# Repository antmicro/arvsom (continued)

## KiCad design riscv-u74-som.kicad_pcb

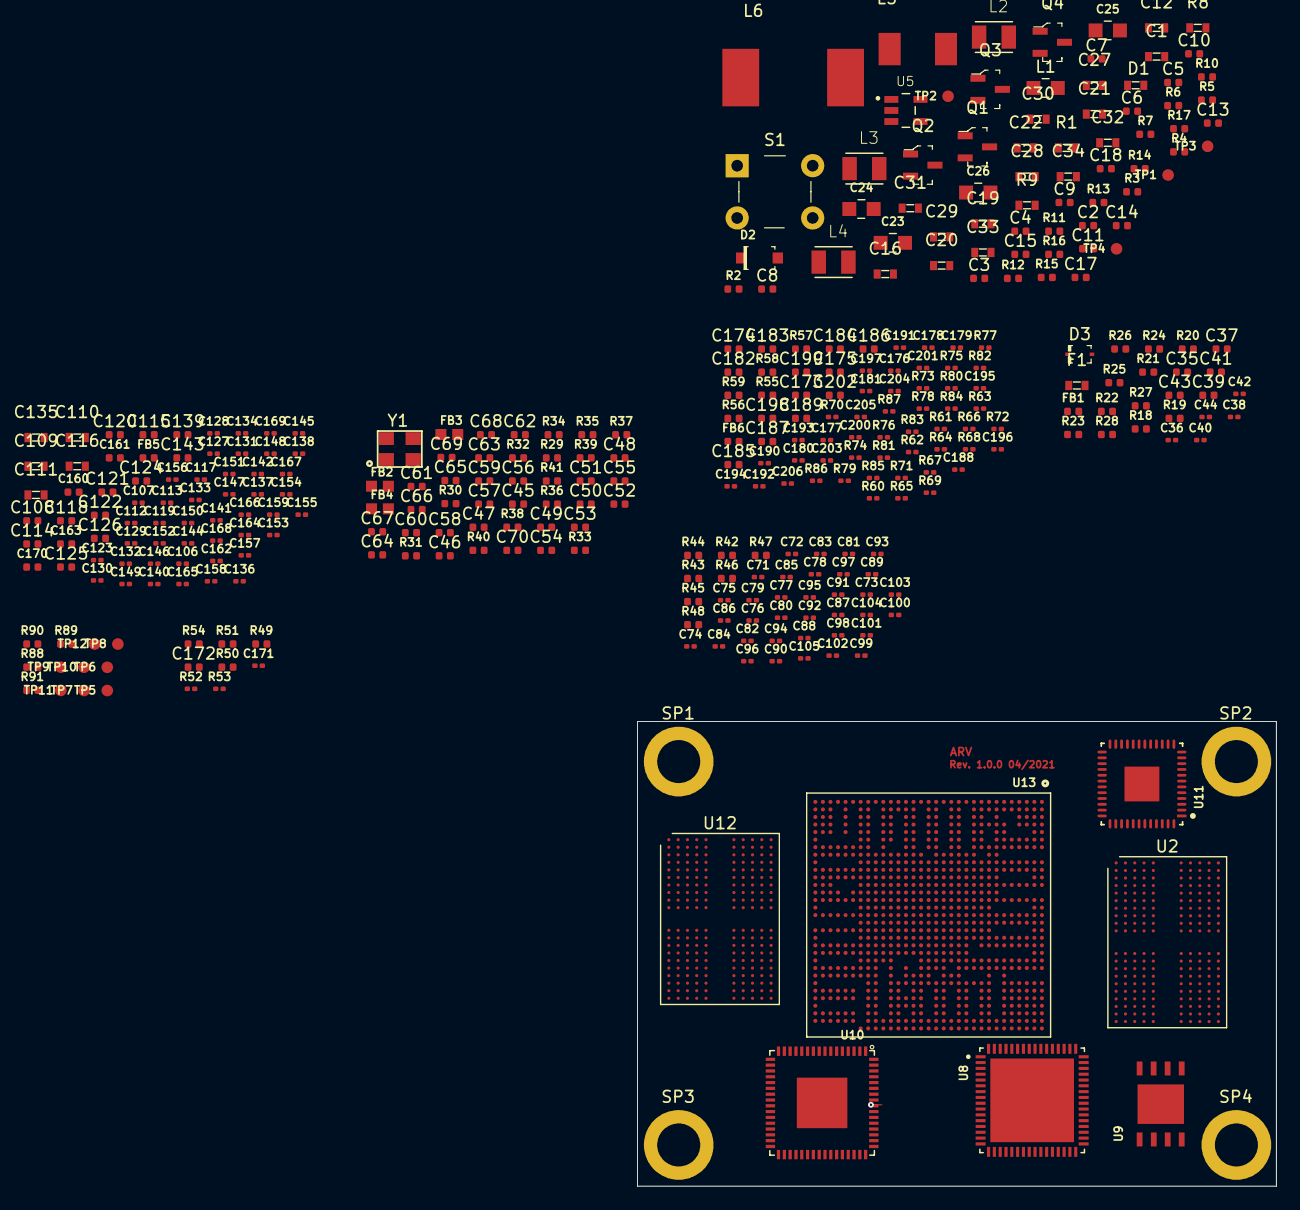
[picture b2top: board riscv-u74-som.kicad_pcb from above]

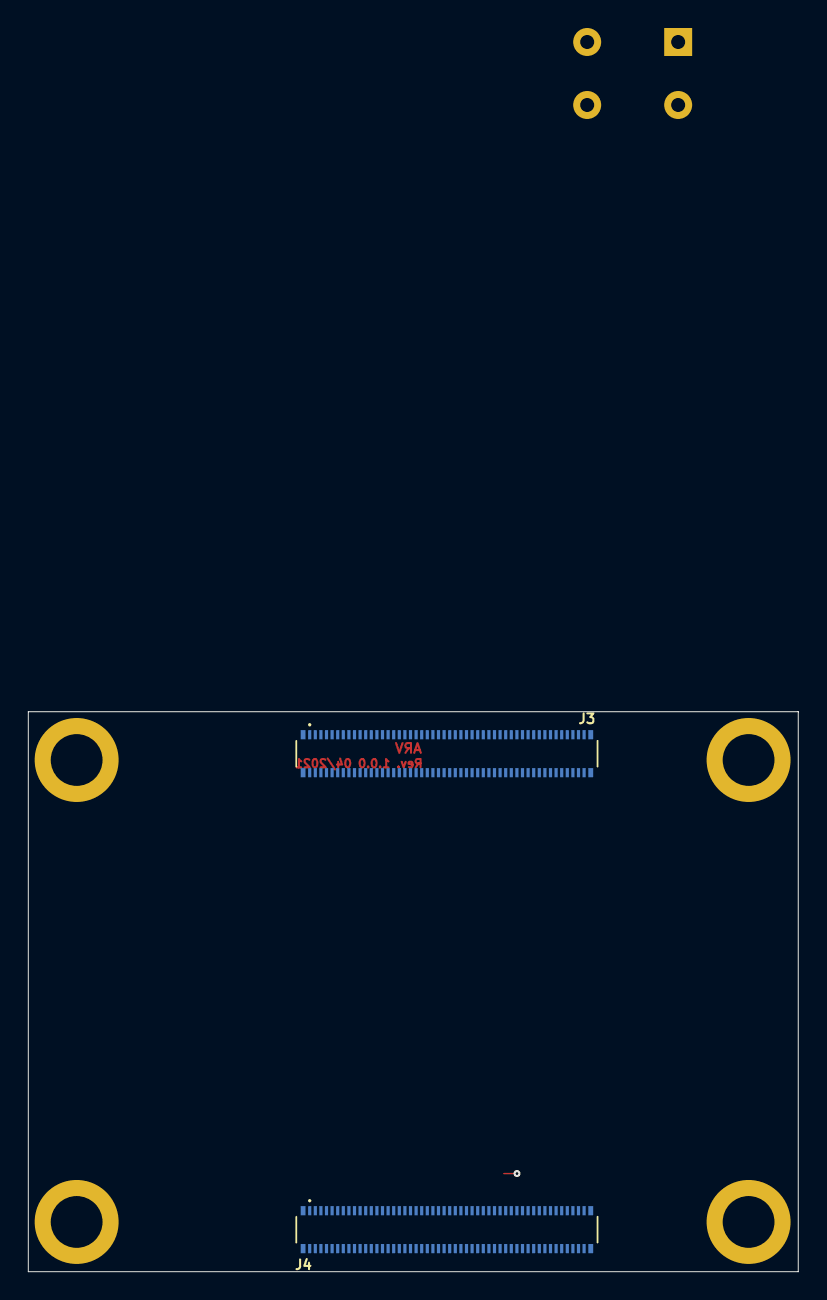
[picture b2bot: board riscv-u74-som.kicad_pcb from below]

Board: 2 copper layers, 55.0 x 40.0 mm, 345 parts (2 on the bottom side), 236 nets.

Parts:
C1, C16, C27, C28: C_10u_0603; 0603-cap
C2, C3, C4, C5, C7, C8, C9, C15, C37, C39, C41, C43: C_2u2_0402; 0402-cap
C6, C11, C14, C45, C47, C49, C50, C58: C_4u7_0402; 0402-cap
C10, C13, C17, C18: C_100n_0402_16V; 0402-cap
C12: C_1n_0603; 0603-cap
C19, C20, C21, C22, C29, C30, C31, C32, C33, C34, C109, C110, C111, C116, C135: C_22u_0603; 0603-cap
C23, C24, C25, C26: C_100u_0805; 0805-cap
C35, C108, C124, C125, C126, C143, C173, C174, C175, C183, C185, C186, C187, C189, C198, C199, C202: C_1u_0402; 0402-cap
C36, C38, C40, C42, C44, C71, C72, C73, C74, C75, C76, C77, C78, C79, C80, C81, C82, C83, C84, C85, C86, C87, C88, C89, C90, C91, C92, C93, C94, C95, C96, C97, C98, C99, C100, C101, C102, C103, C104, C105, C106, C107, C112, C113, C117, C119, C123, C127, C128, C129, C130, C131, C132, C133, C134, C136, C137, C138, C140, C141, C142, C144, C145, C146, C147, C148, C149, C150, C151, C152, C153, C154, C155, C156, C157, C158, C159, C162, C164, C165, C166, C167, C168, C169, C171, C176, C177, C178, C179, C180, C181, C188, C190, C191, C192, C193, C194, C195, C196, C197, C200, C201, C203, C204, C205, C206: C_100n_0201; 0201-res
C46, C48, C51, C52, C53: C_470n_0402; 0402-cap
C54: C_100n_0402; 0402-cap
C55, C56, C57, C59, C60, C61, C62, C63, C64, C65, C66, C67, C68, C172: C_10n_0402; 0402-cap
C69, C70: C_22p_0402; 0402-cap
C114, C115, C118, C120, C121, C122, C139, C182, C184: C_10u_0402; 0402-cap
C160, C161, C163, C170: C_1n_0402; 0402-res
D1: PGB1010603MR
D2: 1N4148W-TP; SOD-123
D3: 1N4148WS; SOD-323F
F1: 0ZCM0002FF2G; 0603-res
FB1, FB5, FB6: BLM15PD121SN1D; 0402-res
FB2, FB3, FB4: BLM18AG601SN1D; 0603
J3, J4: DF40C-100DP-0.4V(51); HRS_DF40C-100DP-0.4V(51)
L1: 10uH; 0805-res
L2, L3, L4: LQH32PN1R0NN0L; IND_LQH32PN1R0NN0L
L5: MPX1D0520LR47
L6: IHLP4040DZERR56M01
Q1, Q2, Q3, Q4: BSS138AKA; SOT-23-3
R1: R_1M_0603; 0603-res
R2, R3, R4, R25, R31, R32, R33, R34, R35, R36, R38, R39, R40, R42, R43, R44, R47, R49, R50, R51, R54, R88, R90: R_10k_0402; 0402-res
R5, R6, R10, R11, R12, R14, R15, R16, R46, R48: R_0R_0402; 0402-res
R7: R_2k2_0402; 0402-res
R8: R_549k_0603; 0603-res
R9: R_13k3_0603; 0603-res
R13, R17, R21, R37: R_4k7_0402; 0402-res
R18, R19, R20, R22, R23, R24, R55, R56, R57, R58, R59: R_33R_0402; 0402-res
R26, R27, R29: R_1k_0402; 0402-res
R28: R_27k_0402; 0402-res
R30: R_12k1_0402; 0402-res
R41: R_1M5_0402; 0402-res
R45, R89, R91: R_240R_0402; 0402-res
R52, R53: R_0R_0201; 0201-res
R60, R61, R62, R63, R64, R65, R66, R67, R68, R69, R70, R71, R72, R73, R74, R75, R76, R77, R78, R79, R80, R81, R82, R83, R84, R85, R86, R87: R_33R_0201; 0201-res
S1: B3F-1000; Switch_Tactile_THT_B3F-1xxx
SP1, SP2, SP3, SP4: 9774030151
TP1, TP2, TP3, TP4, TP5, TP6, TP7, TP8, TP9, TP10, TP11, TP12: TP_SMD1MM; Testpoint_smd_1mm
U2: MT53E256M32D2; BGA-200_10.0x14.5mm_Layout12x22_P0.80x0.65mm
U5: LMR62014XMF_NOPB; SOT95P280X145-5N
U8: TPS65086100; QFN50P900X900X80-65N
U9: GD25LQ256DWIGR; 8-WSON-6x5
U10: TDA19988BHN_C1,557; QFN50P900X900X100-65N
U11: KSZ9031RNXCA; QFN-48-Microchip-QFN77-48LD-PL-2
U12: MT53E256M32D2DS-053; BGA-200_10.0x14.5mm_Layout12x22_P0.80x0.65mm
U13: VIC7100; vic7100
Y1: ABM8G-25.000MHZ-18-D2Y-T; KX-7

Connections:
1V8_OUT: J3.88, J3.90
3V3_OUT: J3.84, J3.86
5V0_IN: J3.77, J3.79, J3.81, J3.83, J3.85, J3.87
/Ethernet/AVDDH: C58.1, C63.1, C66.1, FB2.2, U11.1, U11.12
/Ethernet/AVDDL: C47.1, C51.1, C55.1, C60.1, FB4.1, U11.4, U11.9
/Ethernet/AVDDL_PLL: C50.1, C54.1, C59.1, FB3.1, U11.44
/PMIC/FB: C12.2, R8.2, R9.1, U5.3
ATEMP_TEST0: R51.1, U13.U25
ATEMP_TEST1: R50.1, U13.U24
ATEMP_VCAL: C171.1, U13.V24
ATEMP_VSS: R49.1, U13.V25
AVDD3V3_USB: C202.1, C205.1, FB6.1, U13.AA23
AVDD09_PLL: C108.1, C113.1, C119.1, C123.1, FB5.1, U13.U21, U13.U22, U13.V21
CS0_B: R42.1, U12.R4
CSI1RX_CLK_N: J4.40, U13.M30
CSI1RX_CLK_P: J4.42, U13.M31
CSI1RX_D0_N: J4.28, U13.P30
CSI1RX_D0_P: J4.30, U13.P31
CSI1RX_D1_N: J4.34, U13.N30
CSI1RX_D1_P: J4.36, U13.N31
CSI2RX_CLK_N: J4.27, U13.R30
CSI2RX_CLK_P: J4.29, U13.R31
CSI2RX_D0_N: J4.15, U13.U30
CSI2RX_D0_P: J4.17, U13.U31
CSI2RX_D1_N: J4.21, U13.T30
CSI2RX_D1_P: J4.23, U13.T31
CTL5: D1.2, R4.2, S1.3, S1.4, U8.63
DDR0_A00: U12.H2, U12.R2, U13.C10
DDR0_A01: U12.J2, U12.P2, U13.B10
DDR0_A02: U12.H9, U12.R9, U13.A15
DDR0_A03: U12.H10, U12.R10, U13.D10
DDR0_A04: U12.H11, U12.R11, U13.D12
DDR0_A05: U12.J11, U12.P11, U13.E10
DDR0_CK0_N: U12.J8, U13.B14
DDR0_CK0_P: U12.J9, U13.A14
DDR0_CK1_N: U12.P8, U13.B12
DDR0_CK1_P: U12.P9, U13.A12
DDR0_CKE0: U12.J4, U13.C17
DDR0_CKE1: U12.P4, U13.F17
DDR0_PLL_REFOUT_N: TP5.1, U13.D16
DDR0_PLL_REFOUT_P: TP6.1, U13.E16
DDR0_PLL_TESTOUT_N: TP7.1, U13.H19
DDR0_PLL_TESTOUT_P: TP8.1, U13.G19
DDR1_PLL_REFOUT_N: TP9.1, U13.AF21
DDR1_PLL_REFOUT_P: TP10.1, U13.AG21
DDR1_PLL_TESTOUT_N: TP11.1, U13.AK24
DDR1_PLL_TESTOUT_P: TP12.1, U13.AL24
ETH0_N: J3.10, U11.3
ETH0_P: J3.12, U11.2
ETH1_N: J3.6, U11.6
ETH1_P: J3.4, U11.5
ETH2_N: J3.9, U11.8
ETH2_P: J3.11, U11.7
ETH3_N: J3.5, U11.11
ETH3_P: J3.3, U11.10
ETH_LED1: J3.17, R39.1, U11.17
ETH_LED2: J3.15, R40.1, U11.15
ETH_MDC: U11.36, U13.R28
ETH_MDIO: R37.1, U11.37, U13.Y29
ETH_~RESET: R38.1, U11.42
GND: C1.2, C2.1, C3.1, C4.1, C5.1, C6.2, C7.1, C8.1, C9.2, C10.1, C11.1, C13.2, C14.1, C15.2, C16.2, C19.2, C20.2, C21.2, C22.2, C23.2, C24.2, C25.2, C26.2, C27.2, C28.2, C29.2, C30.2, C31.2, C32.2, C33.2, C34.2, C35.2, C36.2, C37.2, C38.2, C39.2, C40.2, C41.2, C42.2, C43.2, C44.2, C45.2, C46.2, C47.2, C48.2, C49.2, C50.2, C51.2, C52.2, C53.2, C54.2, C55.2, C56.2, C57.2, C58.2, C59.2, C60.2, C61.2, C62.2, C63.2, C64.2, C65.2, C66.2, C67.2, C68.2, C69.2, C70.2, C71.2, C72.2, C73.2, C74.2, C75.2, C76.2, C77.2, C78.2, C79.2, C80.2, C81.2, C82.2, C83.2, C84.2, C85.2, C86.2, C87.2, C88.2, C89.2, C90.2, C91.2, C92.2, C93.2, C94.2, C95.2, C96.2, C97.2, C98.2, C99.2, C100.2, C101.2, C102.2, C103.2, C104.2, C105.2, C106.2, C107.2, C108.2, C109.2, C110.2, C111.2, C112.2, C113.2, C114.2, C115.2, C116.2, C117.2, C118.2, C119.2, C120.2, C121.2, C122.2, C123.2, C124.2, C125.2, C126.2, C127.2, C128.2, C129.2, C130.2, C131.2, C132.2, C133.2, C134.2, C135.2, C136.2, C137.2, C138.2, C139.2, C140.2, C141.2, C142.2, C143.2, C144.2, C145.2, C146.2, C147.2, C148.2, C149.2, C150.2, C151.2, C152.2, C153.2, C154.2, C155.2, C156.2, C157.2, C158.2, C159.2, C160.2, C161.2, C162.2, C163.2, C164.2, C165.2, C166.2, C167.2, C168.2, C169.2, C170.2, C171.2, C172.2, C173.2, C174.2, C175.2, C176.2, C177.2, C178.2, C179.2, C180.2, C181.2, C182.2, C183.2, C184.2, C185.2, C186.2, C187.2, C188.2, C189.2, C190.2, C191.2, C192.2, C193.2, C194.2, C195.2, C196.2, C197.2, C198.2, C199.2, C200.2, C201.2, C202.2, C203.2, C204.2, C205.2, C206.2, D1.1, J3.1, J3.2, J3.7, J3.8, J3.13, J3.14, J3.22, J3.23, J3.32, J3.33, J3.42, J3.43, J3.52, J3.53, J3.59, J3.60, J3.65, J3.66, J3.71, J3.74, J3.98, J4.7, J4.8, J4.13, J4.14, J4.19, J4.20, J4.25, J4.26, J4.31, J4.32, J4.37, J4.38, J4.44, J4.50, J4.55, J4.56, J4.61, J4.62, J4.67, J4.68, J4.73, J4.74, J4.79, J4.80, J4.85, J4.86, J4.91, J4.92, J4.97, J4.98, Q2.2, Q4.2, R3.2, R7.1, R9.2, R13.2, R17.2, R25.2, R29.2, R30.1, R42.2, R45.2, R49.2, R50.2, R51.2, R53.2, R89.1, R91.1, S1.1, S1.2, U5.2, U8.1, U8.6, U8.14, U8.18, U8.29, U8.30, U8.34, U8.36, U8.40, U8.48, U8.50, U8.52, U8.61, U8.65, U9.4, U10.19, U10.49, U10.53, U10.54, U10.65, U11.29, U11.49, U12.A3, U12.A10, U12.AB3, U12.AB5, U12.AB8, U12.AB10, U12.C1, U12.C5, U12.C8, U12.C12, U12.D2, U12.D4, U12.D9, U12.D11, U12.E1, U12.E5, U12.E8, U12.E12, U12.G1, U12.G3, U12.G5, U12.G8, U12.G10, U12.G12, U12.J1, U12.J3, U12.J10, U12.J12, U12.K2, U12.K4, U12.K9, U12.K11, U12.N2, U12.N4, U12.N9, U12.N11, U12.P1, U12.P3, U12.P10, U12.P12, U12.T1, U12.T3, U12.T5, U12.T8, U12.T10, U12.T12, U12.V1, U12.V5, U12.V8, U12.V12, U12.W2, U12.W4, U12.W9, U12.W11, U12.Y1, U12.Y5, U12.Y8, U12.Y12, U13.A4, U13.A7, U13.A11, U13.A18, U13.AA8, U13.AA10, U13.AA12, U13.AA13, U13.AA14, U13.AA15, U13.AA17, U13.AA19, U13.AA20, U13.AA22, U13.AA24, U13.AA29, U13.AB3, U13.AB8, U13.AB10, U13.AB11, U13.AB17, U13.AB19, U13.AB20, U13.AB22, U13.AC8, U13.AC9, U13.AC10, U13.AC14, U13.AC15, U13.AC17, U13.AC19, U13.AC20, U13.AC22, U13.AC24, U13.AC25, U13.AD13, U13.AD14, U13.AD15, U13.AD19, U13.AD20, U13.AD21, U13.AD22, U13.AD25, U13.AD28, U13.AD29, U13.AE3, U13.AE8, U13.AE11, U13.AE14, U13.AE15, U13.AE20, U13.AE23, U13.AE24, U13.AE31, U13.AF27, U13.AG5, U13.AG18, U13.AG24, U13.AH7, U13.AH10, U13.AH13, U13.AH16, U13.AH26, U13.AH29, U13.AJ21, U13.AJ23, U13.AK3, U13.AK5, U13.AK26, U13.AL6, U13.AL9, U13.AL12, U13.AL15, U13.AL19, U13.AL22, U13.AL25, U13.AL28, U13.B21, U13.C1, U13.D2, U13.D9, U13.D23, U13.D27, U13.D28, U13.D29, U13.D30, U13.D31, U13.E2, U13.E17, U13.E29, U13.E30, U13.F7, U13.F16, U13.F20, U13.F24, U13.F29, U13.G3, U13.G13, U13.G16, U13.G20, U13.G22, U13.H7, U13.H9, U13.H10, U13.H16, U13.H17, U13.H18, U13.H20, U13.J9, U13.J10, U13.J12, U13.J16, U13.J17, U13.J22, U13.J23, U13.K3, U13.K5, U13.K8, U13.K9, U13.K10, U13.K11, U13.K22, U13.K23, U13.K25, U13.L8, U13.L9, U13.L10, U13.L11, U13.L12, U13.L13, U13.L16, U13.L18, U13.L19, U13.L20, U13.L22, U13.L23, U13.L28, U13.M10, U13.M11, U13.M12, U13.M13, U13.M14, U13.M15, U13.M16, U13.M17, U13.M18, U13.M20, U13.M22, U13.M24, U13.M25, U13.M26, U13.M27, U13.N3, U13.N12, U13.N15, U13.N16, U13.N17, U13.N18, U13.N20, U13.N22, U13.N24, U13.N25, U13.P12, U13.P14, U13.P15, U13.P18, U13.P20, U13.P22, U13.P24, U13.R12, U13.R14, U13.R15, U13.R20, U13.R22, U13.R23, U13.T3, U13.T9, U13.T10, U13.T11, U13.T12, U13.T14, U13.T22, U13.T24, U13.T25, U13.U8, U13.U9, U13.U10, U13.U11, U13.U12, U13.U13, U13.U18, U13.U19, U13.U20, U13.U23, U13.V10, U13.V11, U13.V12, U13.V13, U13.V18, U13.V19, U13.V20, U13.W3, U13.W10, U13.W12, U13.W13, U13.W20, U13.W21, U13.W24, U13.W25, U13.W30, U13.W31, U13.Y8, U13.Y9, U13.Y10, U13.Y14, U13.Y16, U13.Y17, U13.Y18, U13.Y19, U13.Y20, Y1.2, Y1.4
HDMI_1V8: C37.1, C38.1, C39.1, C40.1, C41.1, C42.1, C43.1, C44.1, FB1.1, U10.5, U10.14, U10.29, U10.35, U10.36, U10.41, U10.46, U10.47, U10.48, U10.55
HDMI_CEC: D3.K, J4.51, U10.30
HDMI_DSCL: J4.100, R27.2, U10.33
HDMI_DSDA: J4.99, R26.2, U10.32
HDMI_HPD: J4.53, U10.31
HDMI_SWING: R25.1, U10.34
HDMI_TX0_N: J4.84, U10.39
HDMI_TX0_P: J4.82, U10.40
HDMI_TX1_N: J4.78, U10.42
HDMI_TX1_P: J4.76, U10.43
HDMI_TX2_N: J4.72, U10.44
HDMI_TX2_P: J4.70, U10.45
HDMI_TXC_N: J4.90, U10.37
HDMI_TXC_P: J4.88, U10.38
I2C0_SCL: J3.80, R5.1, U13.V1
I2C0_SDA: J3.82, R6.1, U13.T4
LCD_DATA0: U10.63, U13.AA5
LCD_DATA1: U10.62, U13.AA6
LCD_DATA2: U10.61, U13.AB1
LCD_DATA3: U10.60, U13.AA2
LCD_DATA4: U10.59, U13.AB5
LCD_DATA5: U10.58, U13.AB6
LCD_DATA6: U10.57, U13.AC1
LCD_DATA7: U10.56, U13.AB2
LCD_DATA8: U10.9, U13.AB7
LCD_DATA9: U10.8, U13.AG2
LCD_DATA10: U10.7, U13.AD1
LCD_DATA11: U10.6, U13.AB4
LCD_DATA13: U10.2, U13.AG3
LCD_DATA14: U10.1, U13.AE1
LCD_DATA15: U10.64, U13.AD2
LCD_DATA16: U10.18, U13.AL3
LCD_DATA17: U10.17, U13.AG4
LCD_DATA18: U10.16, U13.AD3
LCD_DATA19: U10.15, U13.AE2
LCD_DATA20: U10.13, U13.AE4
LCD_DATA22: U10.11, U13.AD4
LCD_DATA23: U10.10, U13.AD5
LCD_DE: U10.20, U13.AA4
LCD_HSYNC: U10.22, U13.Y2
LCD_PCLK: U10.4, U13.AA3
LCD_VSYNC: U10.21, U13.AA1
LDO_3V3: C4.2, U8.21
unnamed: C2.2, C3.2, C7.2, C8.2, U8.8, U8.11, U8.24, U8.38
unnamed: C10.2, R7.2, U8.31
unnamed: C11.2, U8.56
unnamed: C13.1, U8.53
unnamed: C14.2, U8.54
unnamed: C17.1, R10.2
unnamed: C17.2, L5.1, Q1.2, Q2.3, U8.4
unnamed: C18.1, R14.2
unnamed: C18.2, L6.1, Q3.2, Q4.3, U8.42
unnamed: C69.1, R41.1, U11.45, Y1.1
unnamed: C70.1, R41.2, U11.46, Y1.3
unnamed: D2.A, L1.2, U5.1
unnamed: D3.A, R28.1
unnamed: F1.1, R26.1, R27.1
unnamed: L2.1, U8.10
unnamed: L3.1, U8.25
unnamed: L4.1, U8.20
unnamed: Q1.1, R11.2
unnamed: Q2.1, R12.2
unnamed: Q3.1, R15.2
unnamed: Q4.1, R16.2
unnamed: R1.2, U5.4
unnamed: R5.2, TP1.1, U8.58
unnamed: R6.2, TP2.1, U8.59
unnamed: R10.1, U8.5
unnamed: R11.1, U8.3
unnamed: R12.1, U8.7
unnamed: R13.1, U8.64
unnamed: R14.1, U8.41
unnamed: R15.1, U8.43
unnamed: R16.1, U8.39
unnamed: R17.1, U8.45
unnamed: R18.2, R21.2, U9.1
unnamed: R19.2, U9.2
unnamed: R20.2, U9.3
unnamed: R22.1, U9.7
unnamed: R23.1, U9.6
unnamed: R30.2, U11.48
unnamed: R43.2, R46.1, U12.G2
unnamed: R44.2, U12.T2
unnamed: R45.1, U12.A5
unnamed: R47.2, R48.1, U12.T11
unnamed: R55.2, U13.V5
unnamed: R56.2, U13.V3
unnamed: R57.2, U13.V4
unnamed: R58.2, U13.W5
unnamed: R59.2, U13.V7
unnamed: R88.2, U13.C16
unnamed: R89.2, U13.E12
unnamed: R90.2, U13.AJ20
unnamed: R91.2, U13.AG20
unnamed: TP3.1, U8.62
unnamed: TP4.1, U8.15
unnamed: U2.A4, U2.A9, U2.F5, U2.F8, U2.H1, U2.H5, U2.H8, U2.H12, U2.K1, U2.K3, U2.K10, U2.K12
unnamed: U2.A3, U2.A10, U2.C1, U2.C5, U2.C8, U2.C12, U2.D2, U2.D4, U2.D9, U2.D11, U2.E1, U2.E5, U2.E8, U2.E12, U2.G1, U2.G3, U2.G5, U2.G8, U2.G10, U2.G12, U2.J1, U2.J3, U2.J10, U2.J12, U2.K2, U2.K4, U2.K9, U2.K11
unnamed: U2.AA3, U2.AA5, U2.AA8, U2.AA10, U2.U3, U2.U10, U2.W1, U2.W5, U2.W8, U2.W12
unnamed: U2.AB4, U2.AB9, U2.N1, U2.N3, U2.N10, U2.N12, U2.R1, U2.R5, U2.R8, U2.R12, U2.U5, U2.U8
unnamed: U2.AB3, U2.AB5, U2.AB8, U2.AB10, U2.N2, U2.N4, U2.N9, U2.N11, U2.P1, U2.P3, U2.P10, U2.P12, U2.T1, U2.T3, U2.T5, U2.T8, U2.T10, U2.T12, U2.V1, U2.V5, U2.V8, U2.V12, U2.W2, U2.W4, U2.W9, U2.W11, U2.Y1, U2.Y5, U2.Y8, U2.Y12
unnamed: U2.B3, U2.B5, U2.B8, U2.B10, U2.D1, U2.D5, U2.D8, U2.D12, U2.F3, U2.F10
unnamed: U2.F1, U2.F12, U2.G4, U2.G9
unnamed: U2.T4, U2.T9, U2.U1, U2.U12
QSPI_CLK: R23.2, U13.R25
QSPI_D0: R24.2, U13.R26
QSPI_D1: R19.1, U13.R27
QSPI_D2: R20.1, U13.P26
QSPI_D3: R22.2, U13.P25
RESERVED: J3.76, J4.4, J4.6
RGMII_REF_CLK: R36.1, U11.41
RGMII_RXD0: R31.1, U11.32, U13.P28
RGMII_RXD1: R32.1, U11.31, U13.V28
RGMII_RXD2: R33.1, U11.28, U13.U28
RGMII_RXD3: R34.1, U11.27, U13.V26
RGMII_RX_CLK: R35.1, U11.35, U13.V27
RGMII_RX_DV: R29.1, U11.33, U13.AA31
RGMII_TXD0: U11.19, U13.AB31
RGMII_TXD1: U11.20, U13.AA26
RGMII_TXD2: U11.21, U13.AA25
RGMII_TXD3: U11.22, U13.V29
RGMII_TX_CLK: U11.24, U13.AA27
RPI_GPIO2: J3.58, U13.E1
RPI_GPIO3: J3.56, U13.D1
RPI_GPIO4: J3.54, U13.F2
RPI_GPIO5: J3.34, U13.K4
RPI_GPIO6: J3.30, U13.G4
RPI_GPIO7: J3.37, U13.J6
RPI_GPIO8: J3.39, U13.J3
RPI_GPIO9: J3.40, U13.F5
RPI_GPIO10: J3.44, U13.H1
RPI_GPIO11: J3.38, U13.F1
RPI_GPIO12: J3.31, U13.J5
RPI_GPIO13: J3.28, U13.K6
RPI_GPIO14: J3.55, U13.J4
RPI_GPIO15: J3.51, U13.K7
RPI_GPIO16: J3.29, U13.H4
RPI_GPIO17: J3.50, U13.G2
RPI_GPIO18: J3.49, U13.J7
RPI_GPIO19: J3.26, U13.J1
RPI_GPIO20: J3.27, U13.L1
RPI_GPIO21: J3.25, U13.K1
RPI_GPIO22: J3.46, U13.F6
RPI_GPIO23: J3.47, U13.G5
RPI_GPIO24: J3.45, U13.H2
RPI_GPIO25: J3.41, U13.G1
RPI_GPIO26: J3.24, U13.K2
RPI_GPIO27: J3.48, U13.G6
RPI_ID_SC: J3.35, U13.F4
RPI_ID_SD: J3.36, U13.J2
SDIO0_CLK: J3.57, U13.T6
SDIO0_CMD: J3.62, U13.T7
SDIO0_D0: J3.63, U13.R5
SDIO0_D1: J3.67, U13.R4
SDIO0_D2: J3.69, U13.R3
SDIO0_D3: J3.61, U13.R2
SYS_RSTN: C172.1, R2.2, R54.2, U8.27, U13.L29
TEST_MODE: R52.2, R53.1, U13.M29
USBDM_N: J4.3, U13.AC29
USBDP_P: J4.5, U13.AC28
VCC1V2: C45.1, C46.1, C48.1, C52.1, C56.1, C61.1, C64.1, C67.1, C68.1, FB3.2, FB4.2, U11.14, U11.18, U11.23, U11.26, U11.30, U11.39
VCC3V3: C49.1, C53.1, C57.1, C62.1, C65.1, FB2.1, R31.2, R32.2, R33.2, R34.2, R35.2, R36.2, R37.2, R38.2, R39.2, R40.2, U11.16, U11.34, U11.40
VCC_0V9: C23.1, C24.1, C25.1, C26.1, C27.1, C28.1, C106.1, C111.1, C112.1, C116.1, C118.1, C122.1, C126.1, C129.1, C132.1, C136.1, C140.1, C144.1, C148.1, C152.1, C156.1, C162.1, C164.1, C165.1, C166.1, C167.1, C168.1, C169.1, C170.1, C183.1, C186.1, C189.1, C192.1, C195.1, C197.1, FB5.2, L5.2, U8.2, U13.AA11, U13.AA18, U13.AC23, U13.AD23, U13.L17, U13.L21, U13.M19, U13.M21, U13.N19, U13.N21, U13.P16, U13.P17, U13.P19, U13.P21, U13.P23, U13.R16, U13.R17, U13.R18, U13.R19, U13.R21, U13.T15, U13.T16, U13.T17, U13.T18, U13.T19, U13.T20, U13.T21, U13.U14, U13.U15, U13.U16, U13.U17, U13.V14, U13.V15, U13.V16, U13.V17, U13.W11, U13.W14, U13.W15, U13.W16, U13.W17, U13.W18, U13.W19, U13.Y11, U13.Y12, U13.Y13, U13.Y15
VCC_1V1: C107.1, C109.1, C110.1, C114.1, C115.1, C117.1, C120.1, C121.1, C124.1, C125.1, C127.1, C128.1, C130.1, C131.1, C133.1, C134.1, C137.1, C138.1, C141.1, C142.1, C145.1, C146.1, C149.1, C150.1, C153.1, C154.1, C157.1, C158.1, C160.1, C161.1, L6.2, R88.1, R90.1, U8.44, U8.46, U13.AA16, U13.AB12, U13.AB13, U13.AB14, U13.AB15, U13.AB16, U13.AB18, U13.AC11, U13.AC12, U13.AC13, U13.AC16, U13.AC18, U13.AD8, U13.AD9, U13.AD10, U13.AD11, U13.AD12, U13.AD16, U13.AD17, U13.AD18, U13.AE9, U13.AE10, U13.AE12, U13.AE17, U13.AE19, U13.AE21, U13.AE22, U13.G7, U13.G8, U13.G9, U13.G10, U13.G11, U13.H8, U13.H11, U13.H12, U13.H13, U13.H14, U13.H15, U13.J11, U13.J13, U13.J14, U13.J15, U13.J18, U13.J19, U13.J20, U13.K12, U13.K13, U13.K14, U13.K15, U13.K16, U13.K17, U13.K18, U13.K19, U13.L14, U13.L15
VCC_1V2: C33.1, C34.1, L4.2, U8.22
VCC_1V8: C5.2, C30.1, C32.1, C35.1, C36.1, C135.1, C139.1, C143.1, C147.1, C151.1, C155.1, C159.1, C163.1, C173.1, C174.1, C175.1, C176.1, C177.1, C178.1, C179.1, C180.1, C181.1, FB1.2, L3.2, R2.1, R4.1, R21.1, R52.1, R54.1, U8.23, U8.32, U9.8, U13.AB21, U13.AD24, U13.M8, U13.M9, U13.M23, U13.N8, U13.N9, U13.N10, U13.N11, U13.P8, U13.P9, U13.P10, U13.P11, U13.R8, U13.R9, U13.R10, U13.R11, U13.T23, U13.W23
VCC_3V3: C29.1, C31.1, C182.1, C184.1, C185.1, C187.1, C188.1, C190.1, C191.1, C193.1, C194.1, C196.1, C198.1, C199.1, C200.1, C201.1, C203.1, C204.1, C206.1, FB6.2, L2.2, R28.2, U8.12, U13.AA9, U13.AA21, U13.AB9, U13.N13, U13.N14, U13.P13, U13.R13, U13.T13, U13.V8, U13.V9, U13.W8, U13.W9, U13.Y21
VCC_5V0: C1.1, C15.1, C19.1, C20.1, C21.1, C22.1, F1.2, L1.1, Q1.3, Q3.3, R1.1, U5.5, U8.57
VCC_5V8: C12.1, C16.1, D2.K, R8.1
VDD1: C94.1, C95.1, C97.1, C99.1, C101.1, U12.F1, U12.F12, U12.G4, U12.G9, U12.T4, U12.T9, U12.U1, U12.U12
VDD2: C73.1, C76.1, C79.1, C82.1, C85.1, C88.1, C90.1, C92.1, C93.1, C96.1, C98.1, C100.1, C102.1, C103.1, C104.1, C105.1, U12.A4, U12.A9, U12.AB4, U12.AB9, U12.F5, U12.F8, U12.H1, U12.H5, U12.H8, U12.H12, U12.K1, U12.K3, U12.K10, U12.K12, U12.N1, U12.N3, U12.N10, U12.N12, U12.R1, U12.R5, U12.R8, U12.R12, U12.U5, U12.U8
VDD2PEN: R3.1, U8.60, U13.M6
VDD2PEN_OTP_1V8: C6.1, U8.9, U13.AC21
VDDQ: C71.1, C72.1, C74.1, C75.1, C77.1, C78.1, C80.1, C81.1, C83.1, C84.1, C86.1, C87.1, C89.1, C91.1, R43.1, R44.1, R47.1, U12.AA3, U12.AA5, U12.AA8, U12.AA10, U12.B3, U12.B5, U12.B8, U12.B10, U12.D1, U12.D5, U12.D8, U12.D12, U12.F3, U12.F10, U12.U3, U12.U10, U12.W1, U12.W5, U12.W8, U12.W12
VSYS_5V8: C9.1, U8.55

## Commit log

2021-03-18 Initial commit. Added mock design files
2021-03-19 Flipped standoffs in mock PCB
2021-04-08 Added PMIC schematic
2021-04-12 Added decoupling sheet
2021-04-15 Added interfaces, ethernet, LPDDR4
2021-04-19 Added processor and B2B sheets
2021-04-20 Updated B2B connectors sheet
2021-04-20 Changed B2B connectors to headers
2021-04-21 Updated mock
2021-04-22 Connected interfaces to VIC to visualise its ball locations (wip, mock purposes)
2021-04-22 Renamed design files
2021-04-28 Added logotypes
2021-04-28 Added title block settings
2021-04-28 Updated DDR MPN
2021-04-28 B2B updated
2021-04-28 Schematic cleanup, added logotypes
2021-04-28 Added .gitignore
2021-04-28 Added 3D visualisation to main schematic
2021-04-28 Minor mock update
2021-04-28 Marked BT, WiFi, DAC pins as NC, added ACK LED
2021-04-28 Updated interfaces, CPU and B2B connector connections
2021-04-28 Removed decoupling sheet (unused)
2021-04-28 PMIC restored
2021-04-28 Changes to VIC config after review
2021-04-28 Added I2C0 pullups, minor interfaces changes
2021-04-28 Added SDIO CD pulldown
2021-04-28 PMIC fixed and cleaned
2021-04-28 Minor label fix
2021-04-28 Neatened decoupling labels
2021-04-28 Added local libraries
2021-04-28 Added README and license
2021-04-28 Update libraries
2021-04-28 Review README
2021-04-28 Fix typo
2021-04-29 README: Clarify USB variant
2021-04-29 README: Update DRAM info
2021-04-29 Added DDR layout (wip)
2021-04-29 Update 3D Vis
2021-04-29 Update features section
2021-04-29 Update naming convention
2021-04-30 Added basic rules, removed lefover zones, imported components
2021-04-30 Updated PMIC components. PMIC component grouping
2021-04-30 Started PMIC placement
2021-05-04 Fixed power labels on ETH
2021-05-04 PMIC initial placement
2021-05-04 Updated PMIC to match B0.9
2021-05-04 Updated LPDDR4. Fixed reversed clocks
2021-05-05 Updated GPIO pinout to BV0.9. Remapped DSI. Mapped USB3.0
2021-05-05 Update 3DVis
2021-05-05 Updated ethernet and interfaces.sch
2021-05-05 Updated VIC config, added reset and crystals
2021-05-06 Added BOOT_FROM_UART and power LED. Changed LED transistor to smaller footprint
2021-05-06 Added JTAG connector
2021-05-06 Replaced 33R groups with resistor arrays
2021-05-07 Changed VIC pad size
2021-05-10 Added UART3 testpoints
2021-05-10 Fixed two DDR pinout errors
2021-05-11 Corrected error in xODTx lines naming
2021-05-11 Fixed DRC errors in DDR area
2021-05-13 Grouping components for framer placement
2021-05-13 Updated component placement - PHY passives placed, moved HDMI IC, lowered VIC and DDRs
2021-05-14 Updated component placement - HDMI IC passives, QSPI, 5V8 buck placed
2021-05-14 Updated component placement - VIC power decoupling done
2021-05-14 Updated component placement - VIC interfaces decoupling done
2021-05-17 Updated component placement - DDR decoupling done
2021-05-17 Finished component placement
2021-05-19 Updated VIC and SPIFlash footprints
2021-05-19 RGMII sketch, started LCD
2021-05-21 Layout: RGMII, most of LCD
2021-05-21 Layout: GPIO breakout
2021-05-21 HDMI routed
2021-05-24 CSI and DSI routed
2021-05-24 PHY, GPIOs, SDIO connections done
2021-05-24 PCIe/USB routing WIP
2021-05-25 Routed USB, QSPI, JTAG
2021-05-25 Added missing vias, connected more GPIOs
2021-05-26 Placed spare decoupling capacitors under VIC
2021-05-27 Routed DDR decoupling
2021-05-31 VIC decoupling: replaced most GND vias with through-hole
2021-06-01 VIC 1V1 decoupling
2021-06-01 VIC 3V3 decoupling
2021-06-01 VIC 1V8 decoupling
2021-06-01 VIC 0V9 decoupling
2021-06-02 DRC cleanup
2021-06-02 VIC decoupling layout
2021-06-04 PMIC re-worked, layout
2021-06-07 Layout: 5v8 dcdc, clocks, SPIFlash, testpoints
2021-06-08 Layout: reset circuit, testpoints, cleaned JTAG, PHY
2021-06-09 Layout - power planes
2021-06-09 Clenup in HDMI area
2021-06-11 Layout - solved power islands under VIC
2021-06-11 Routed all not connected nets except not placed capacitors
2021-06-14 Caps cleared, module connnetors' GND optimized
2021-06-14 DSI1 routing simplified
2021-06-14 ETH tuned
2021-06-14 Rerouted and length-match HDMI, CSI, DSI signals
2021-06-15 Length matche PCIe, USB (wip), set RGMII net widths
2021-06-15 RGMII tuned
2021-06-15 Top designator arranged
2021-06-15 Adjusted top silkscreen marks
2021-06-16 Designators placed, add missing 3D models
2021-06-16 Update PCB page annotations
2021-06-16 Replace mounting holes, add revision info to PCB
2021-06-16 Revision info soldermask fix
2021-06-16 Update libs
2021-06-17 Update lib attributes
2021-06-24 Notes added by 'git notes add'
2021-08-26 Add PDF schematic
2021-08-26 Cleanup
2022-05-27 Rescale image
2022-05-27 Add badge
2023-03-07 Upgrade design files to Kicad6
2023-03-07 Update README image
2023-03-07 Update PDF schematic
